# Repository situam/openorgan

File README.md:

# Open Organ

A paraphonic analog synthesizer that offers tangible connections to its circuitry. Touch and moisture sensitive traces let the tunable voices flow into the shaping section. Filter, compressor, vibrato, and mixing modules are built in. Sound is also shaped by its power input, inviting musical interaction with the power source.

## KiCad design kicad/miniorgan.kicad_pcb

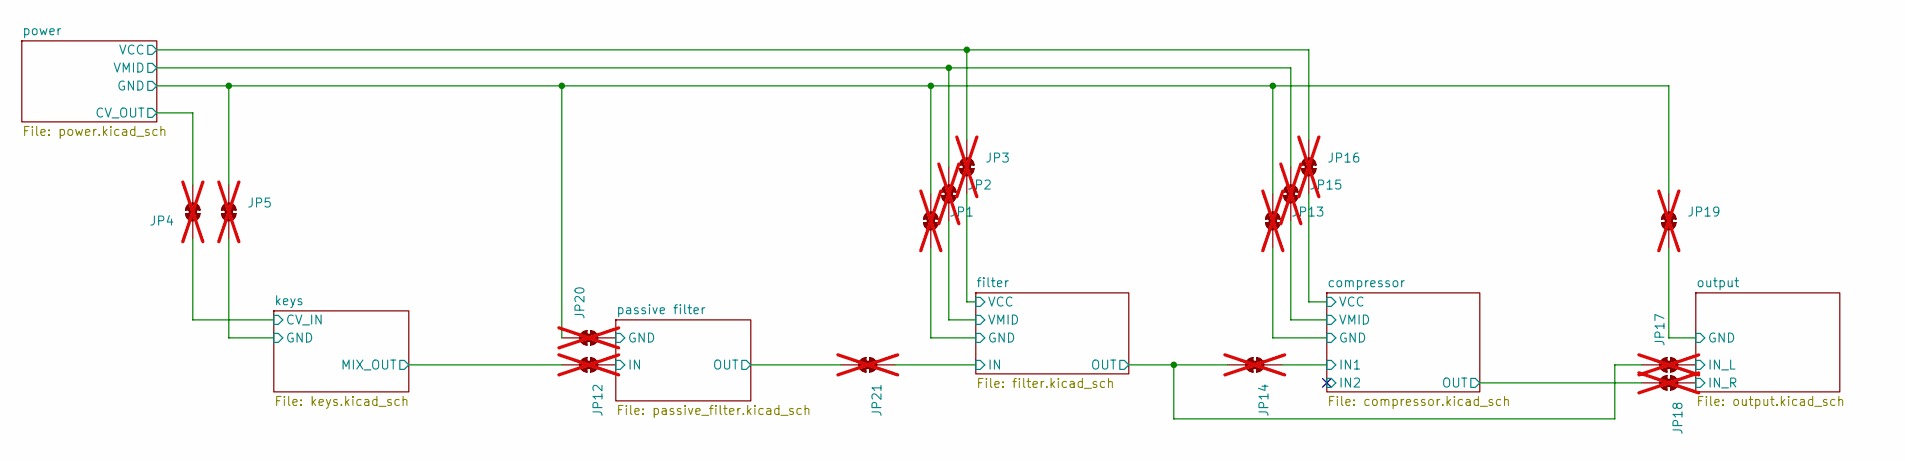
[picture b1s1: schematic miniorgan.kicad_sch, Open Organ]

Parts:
JP1, JP2, JP3, JP4, JP5, JP12, JP13, JP14, JP15, JP16, JP17, JP18, JP19, JP20, JP21: SolderJumper-2_P1.3mm_Bridged_RoundedPad1.0x1.5mm; not fitted

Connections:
/Filter/GND: JP1.2 (B); also elsewhere on the board
/Filter/IN: JP21.1 (A); also elsewhere on the board
/Filter/OUT: JP14.2 (B), JP17.1 (A); also elsewhere on the board
/Filter/VCC: JP3.2 (B); also elsewhere on the board
/Filter/VMID: JP2.2 (B); also elsewhere on the board
/keys/CV_IN: JP4.1 (A); also elsewhere on the board
/keys/GND: JP5.2 (B); also elsewhere on the board
/keys/MIX_OUT: JP12.2 (B); also elsewhere on the board
/output/GND: JP19.2 (B); also elsewhere on the board
/output/IN_L: JP17.2 (B); also elsewhere on the board
/output/IN_R: JP18.1 (A); also elsewhere on the board
/passive filter/GND: JP20.2 (B); also elsewhere on the board
/passive filter/IN: JP12.1 (A); also elsewhere on the board
/passive filter/OUT: JP21.2 (B); also elsewhere on the board
/power/CV_OUT: JP4.2 (B); also elsewhere on the board
/power/GND: JP1.1 (A), JP5.1 (A), JP13.1 (A), JP19.1 (A), JP20.1 (A); also elsewhere on the board
/power/VCC: JP3.1 (A), JP16.1 (A); also elsewhere on the board
/power/VMID: JP2.1 (A), JP15.1 (A); also elsewhere on the board
/vactrol compressor/GND: JP13.2 (B); also elsewhere on the board
/vactrol compressor/IN1: JP14.1 (A); also elsewhere on the board
/vactrol compressor/OUT: JP18.2 (B); also elsewhere on the board
/vactrol compressor/VCC: JP16.2 (B); also elsewhere on the board
/vactrol compressor/VMID: JP15.2 (B); also elsewhere on the board

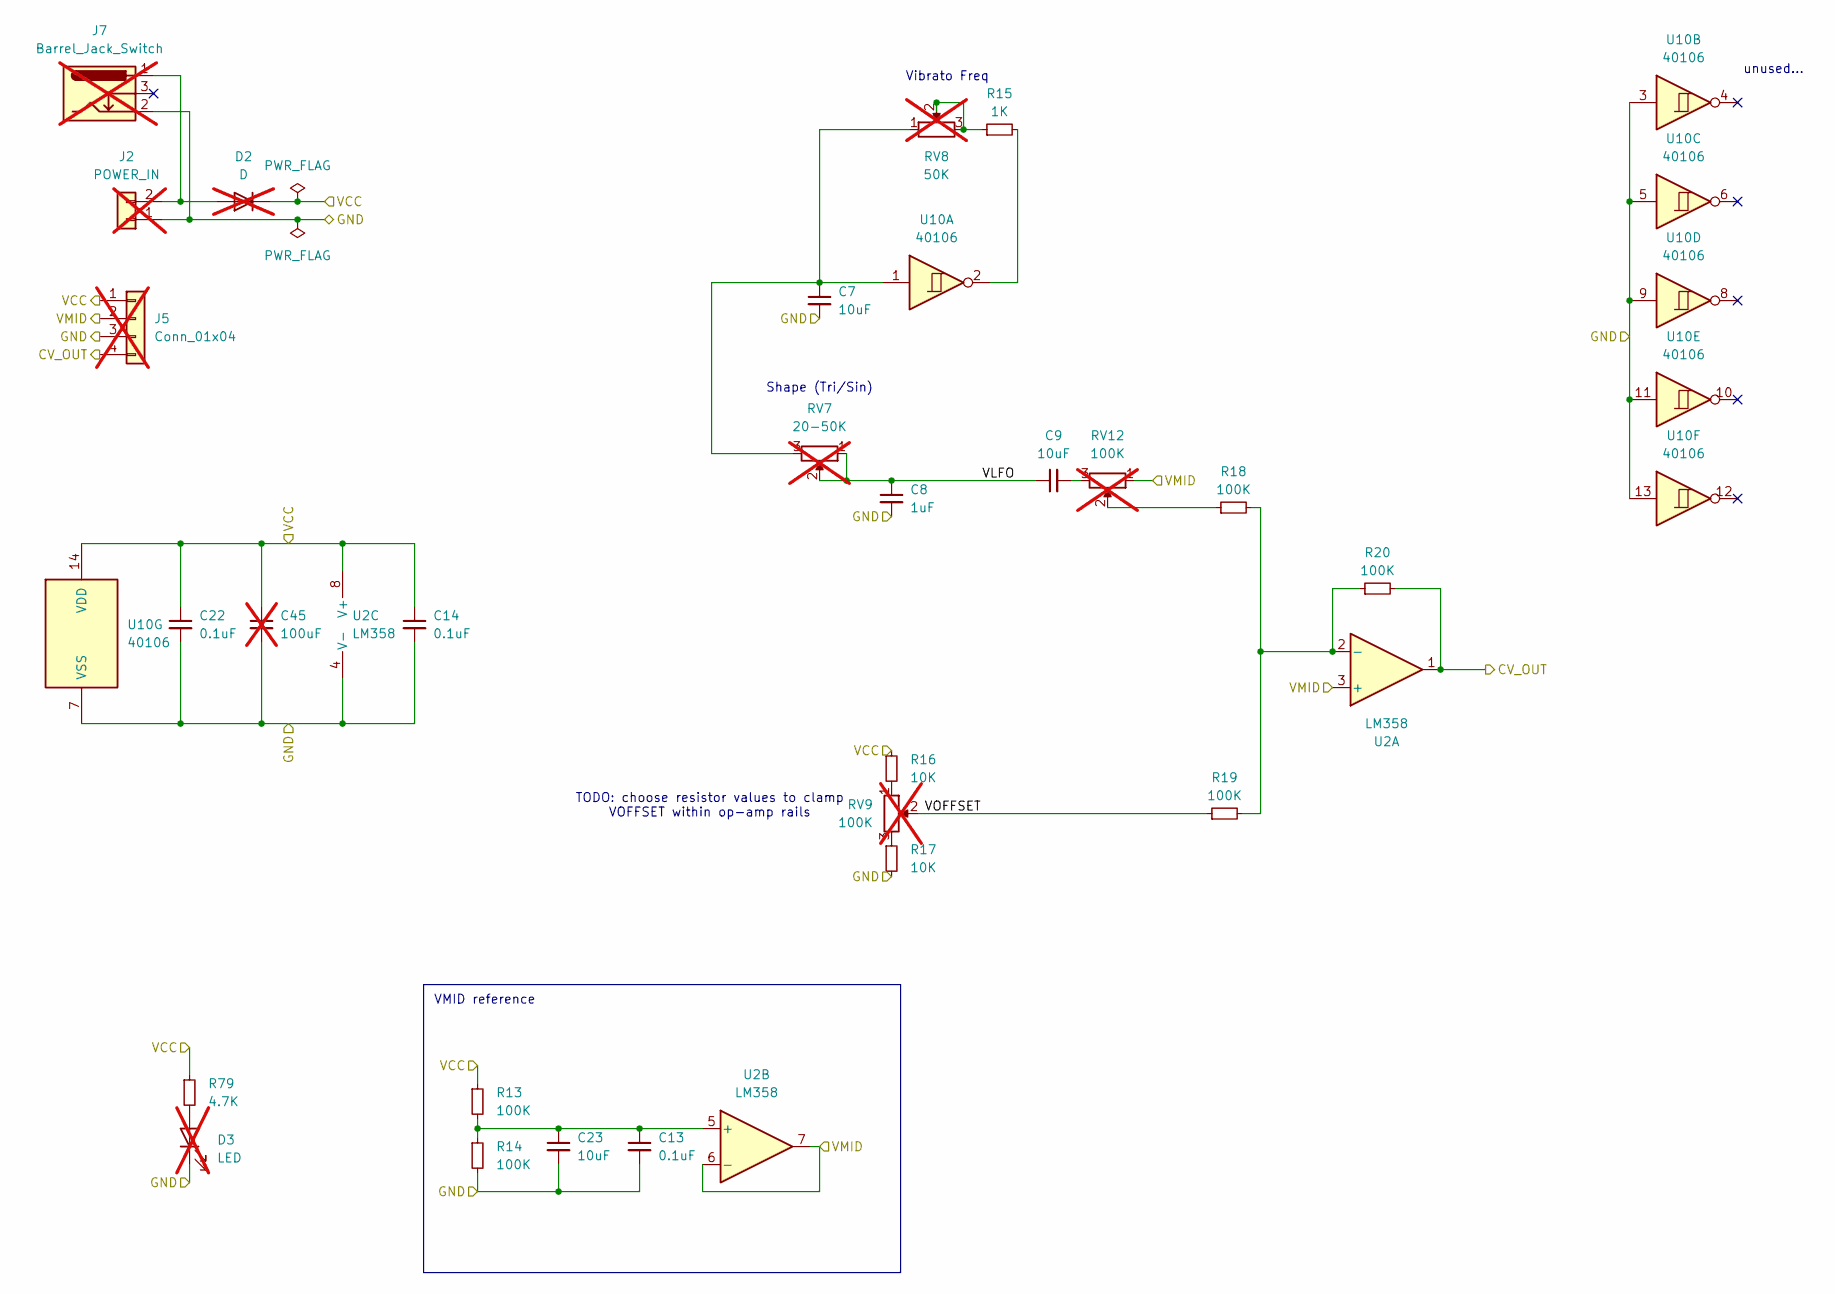
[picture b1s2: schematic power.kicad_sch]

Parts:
C7, C9, C23: 10uF; C_0805_2012Metric
C8: 1uF; C_0805_2012Metric
C13, C14, C22: 0.1uF; C_0805_2012Metric
C45: 100uF; CP_Radial_D7.5mm_P2.50mm; not fitted
D2: D; D_T-1_P2.54mm_Vertical_AnodeUp; not fitted
D3: LED; LED_D3.0mm; not fitted
J2: POWER_IN; PinSocket_1x02_P2.54mm_Vertical; not fitted
J5: Conn_01x04; PinSocket_1x04_P2.54mm_Vertical; not fitted
J7: Barrel_Jack_Switch; BarrelJack_GCT_DCJ200-10-A_Horizontal; not fitted
R13, R14, R18, R19, R20: 100K; R_0603_1608Metric
R15: 1K; R_0603_1608Metric
R16, R17: 10K; R_0603_1608Metric
R79: 4.7K; R_0603_1608Metric
RV7: 20-50K; Pot_RV09AF-ALPHA; not fitted
RV8: 50K; Pot_RV09AF-ALPHA; not fitted
RV9, RV12: 100K; Pot_RV09AF-ALPHA; not fitted
U2: LM358; SOIC-8_L5.0-W4.0-P1.27-LS6.0-BL; JLC C7950
U10: 40106; SOIC-14_L8.7-W3.9-P1.27-LS6.0-BL; JLC C38184

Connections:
/power/CV_OUT: J5.4, R20.2, U2.1; also elsewhere on the board
/power/GND: C7.2, C8.2, C13.2, C14.2, C22.2, C23.2, C45.2, D3.1 (K), J2.1, J5.3, J7.2, R14.2, R17.2, U2.4 (V-), U10.3, U10.5, U10.7 (VSS), U10.9, U10.11, U10.13; also elsewhere on the board
/power/VCC: C14.1, C22.1, C45.1, D2.1 (K), J5.1, R13.1, R16.1, R79.1, U2.8 (V+), U10.14 (VDD); also elsewhere on the board
/power/VLFO: C8.1, C9.1, RV7.1, RV7.2
/power/VMID: J5.2, RV12.1, U2.3 (+), U2.6 (-), U2.7; also elsewhere on the board
/power/VOFFSET: R19.1, RV9.2
unnamed: C7.1, RV7.3, RV8.1, U10.1
unnamed: C9.2, RV12.3
unnamed: D2.2 (A), J2.2, J7.1
unnamed: D3.2 (A), R79.2
unnamed: R15.1, RV8.2, RV8.3
unnamed: R15.2, U10.2
unnamed: R16.2, RV9.1
unnamed: R17.1, RV9.3
unnamed: R18.1, RV12.2
unnamed: R18.2, R19.2, R20.1, U2.2 (-)
unnamed: C13.1, C23.1, R13.2, R14.1, U2.5 (+)

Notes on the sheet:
TODO: choose resistor values to clamp VOFFSET within op-amp rails
Vibrato Freq
Shape (Tri/Sin)
VMID reference
unused...

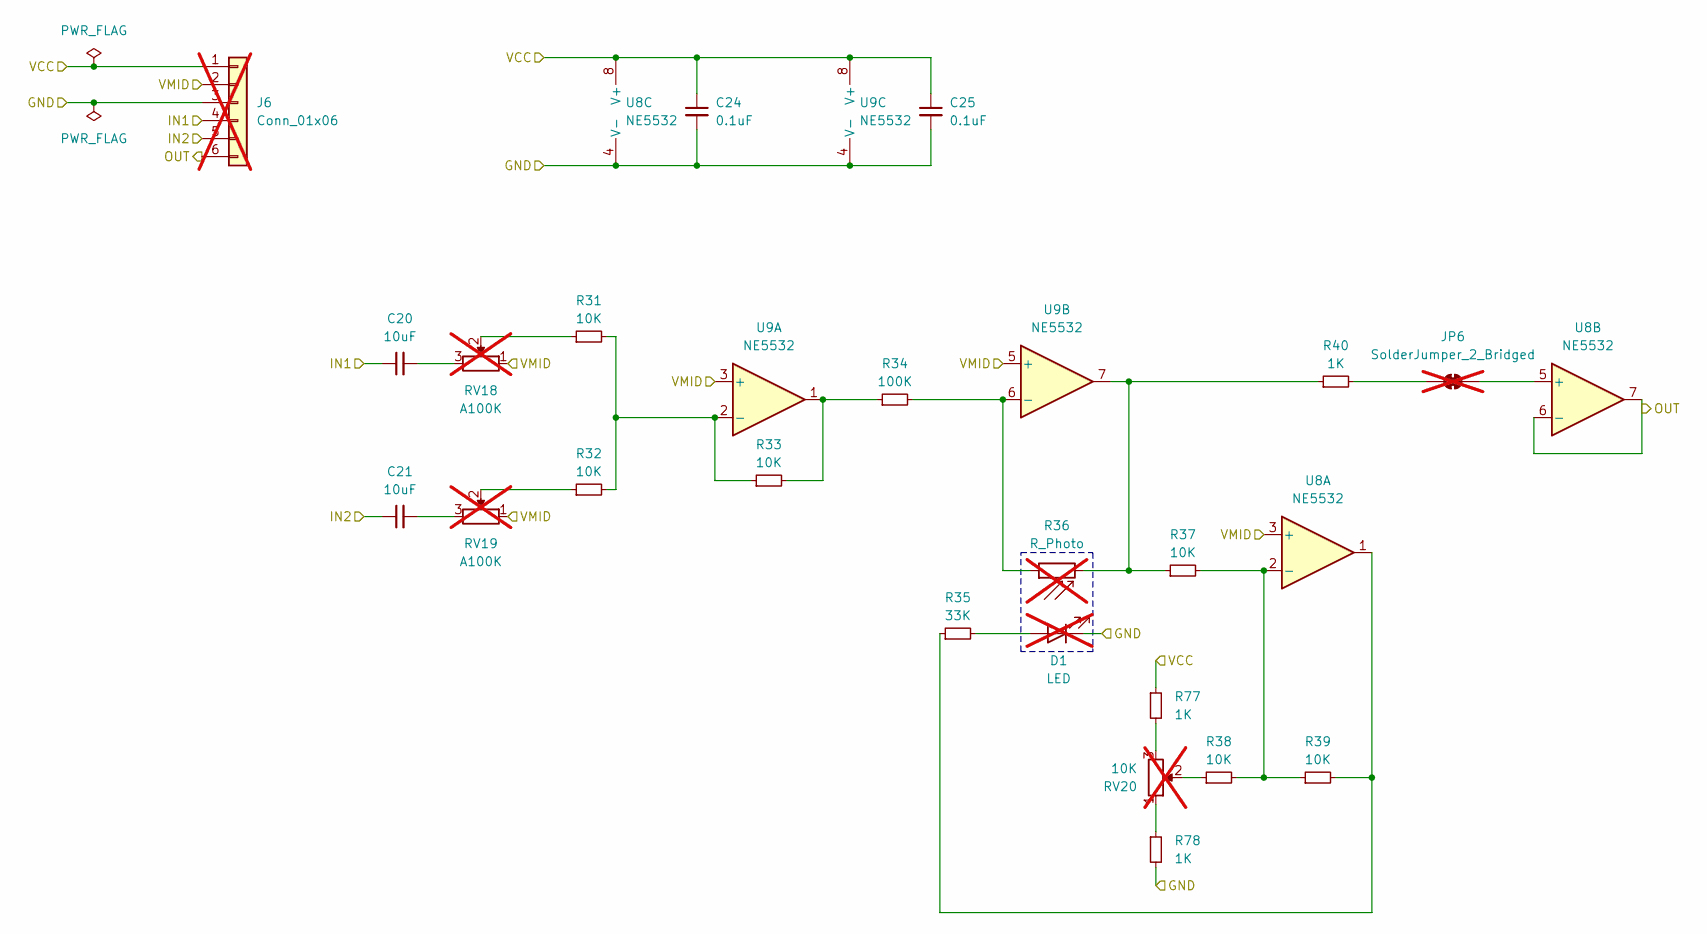
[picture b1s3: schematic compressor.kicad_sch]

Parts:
C20, C21: 10uF; C_0805_2012Metric
C24, C25: 0.1uF; C_0805_2012Metric
D1: LED; LED_D5.0mm_Clear; not fitted
J6: Conn_01x06; PinSocket_1x06_P2.54mm_Vertical; not fitted
JP6: SolderJumper_2_Bridged; SolderJumper-2_P1.3mm_Bridged_RoundedPad1.0x1.5mm; not fitted
R31, R32, R33, R37, R38, R39: 10K; R_0603_1608Metric
R34: 100K; R_0603_1608Metric
R35: 33K; R_0603_1608Metric
R36: R_Photo; R_LDR_4.9x4.2mm_P2.54mm_Vertical; not fitted
R40, R77, R78: 1K; R_0603_1608Metric
RV18, RV19: A100K; Pot_RV09AF-ALPHA; not fitted
RV20: 10K; Pot_RV09AF-ALPHA; not fitted
U8, U9: NE5532; SOIC-8_L4.9-W3.9-P1.27-LS6.0-BL; JLC C7426

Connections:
/vactrol compressor/GND: C24.2, C25.2, D1.1 (K), J6.3, R78.2, U8.4 (V-), U9.4 (V-); also elsewhere on the board
/vactrol compressor/IN1: C20.1, J6.4; also elsewhere on the board
/vactrol compressor/IN2: C21.1, J6.5
/vactrol compressor/OUT: J6.6, U8.6 (-), U8.7; also elsewhere on the board
/vactrol compressor/VCC: C24.1, C25.1, J6.1, R77.1, U8.8 (V+), U9.8 (V+); also elsewhere on the board
/vactrol compressor/VMID: J6.2, RV18.1, RV19.1, U8.3 (+), U9.3 (+), U9.5 (+); also elsewhere on the board
unnamed: C20.2, RV18.3
unnamed: C21.2, RV19.3
unnamed: D1.2 (A), R35.2
unnamed: JP6.1 (A), U8.5 (+)
unnamed: JP6.2 (B), R40.2
unnamed: R31.1, RV18.2
unnamed: R32.1, RV19.2
unnamed: R33.2, R34.1, U9.1
unnamed: R35.1, R39.2, U8.1
unnamed: R36.2, R37.1, R40.1, U9.7
unnamed: R38.1, RV20.2
unnamed: R77.2, RV20.3
unnamed: R78.1, RV20.1
unnamed: R37.2, R38.2, R39.1, U8.2 (-)
unnamed: R31.2, R32.2, R33.1, U9.2 (-)
unnamed: R34.2, R36.1, U9.6 (-)

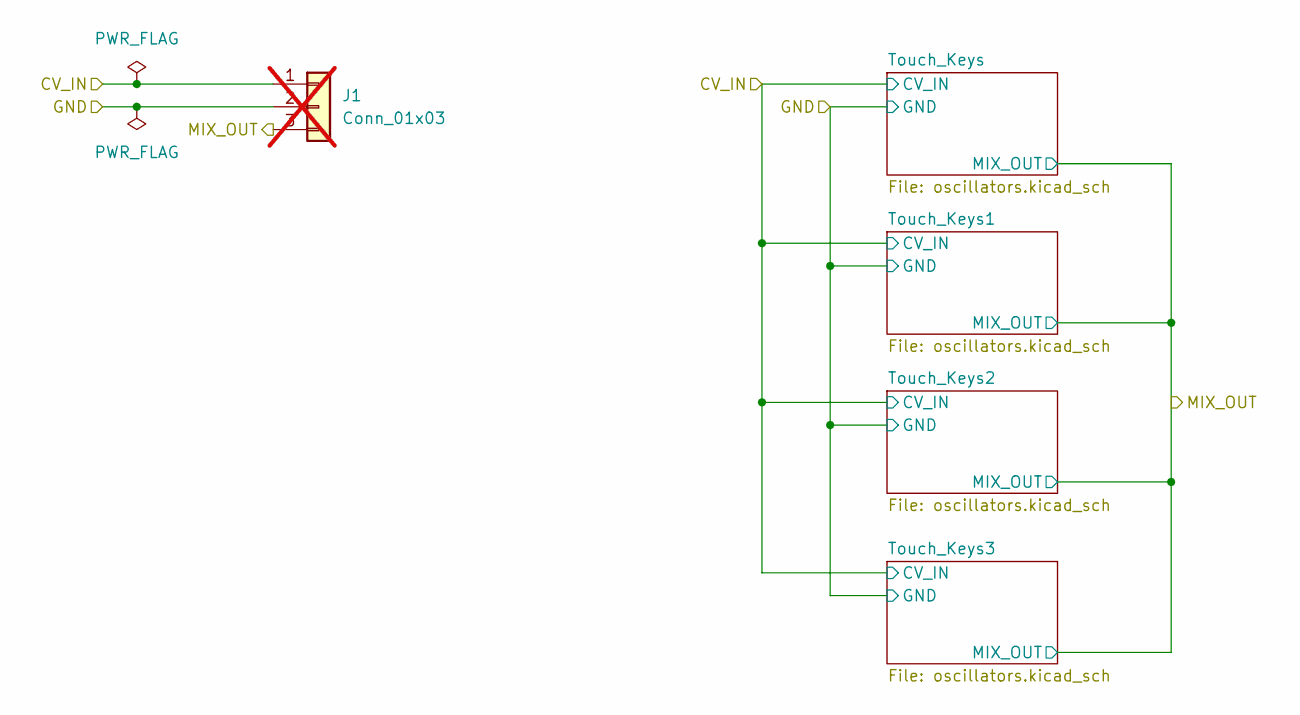
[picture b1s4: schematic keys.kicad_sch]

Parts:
J1: Conn_01x03; PinHeader_1x03_P2.54mm_Vertical; not fitted

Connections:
/keys/CV_IN: J1.1; also elsewhere on the board
/keys/GND: J1.2; also elsewhere on the board
/keys/MIX_OUT: J1.3; also elsewhere on the board

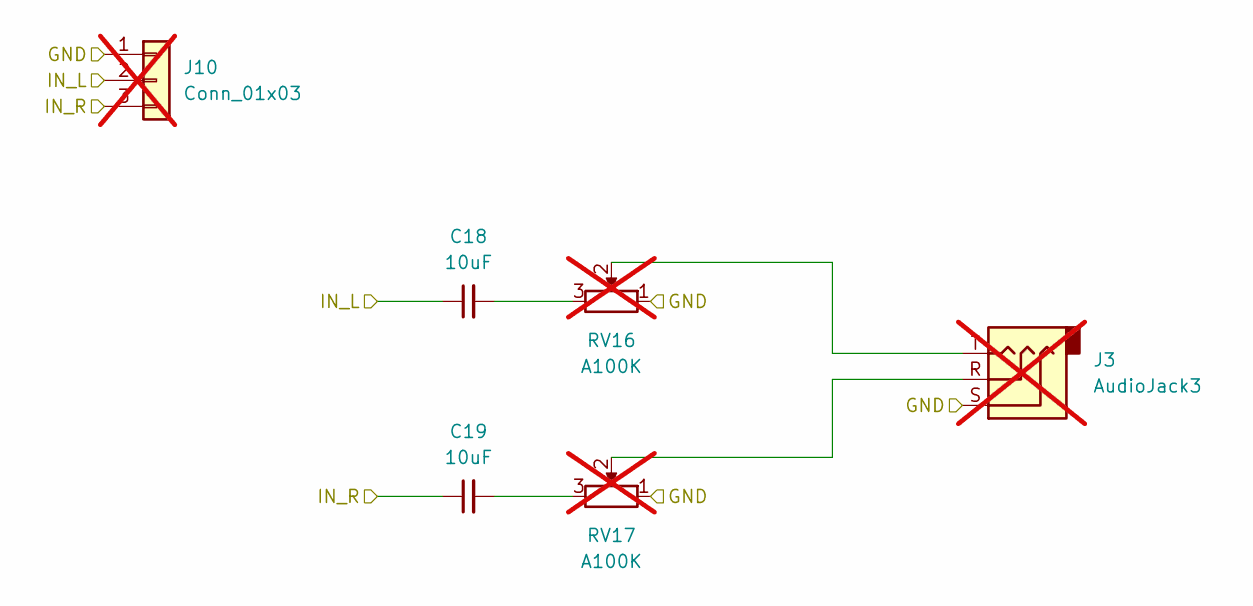
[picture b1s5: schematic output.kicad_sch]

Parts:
C18, C19: 10uF; C_0805_2012Metric
J3: AudioJack3; Jack_3.5mm_CUI_SJ1-3525N_Horizontal; not fitted
J10: Conn_01x03; PinSocket_1x03_P2.54mm_Vertical; not fitted
RV16, RV17: A100K; Pot_RV09AF-ALPHA; not fitted

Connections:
/output/GND: J3.S, J10.1, RV16.1, RV17.1; also elsewhere on the board
/output/IN_L: C18.1, J10.2; also elsewhere on the board
/output/IN_R: C19.1, J10.3; also elsewhere on the board
unnamed: C18.2, RV16.3
unnamed: C19.2, RV17.3
unnamed: J3.R, RV17.2
unnamed: J3.T, RV16.2

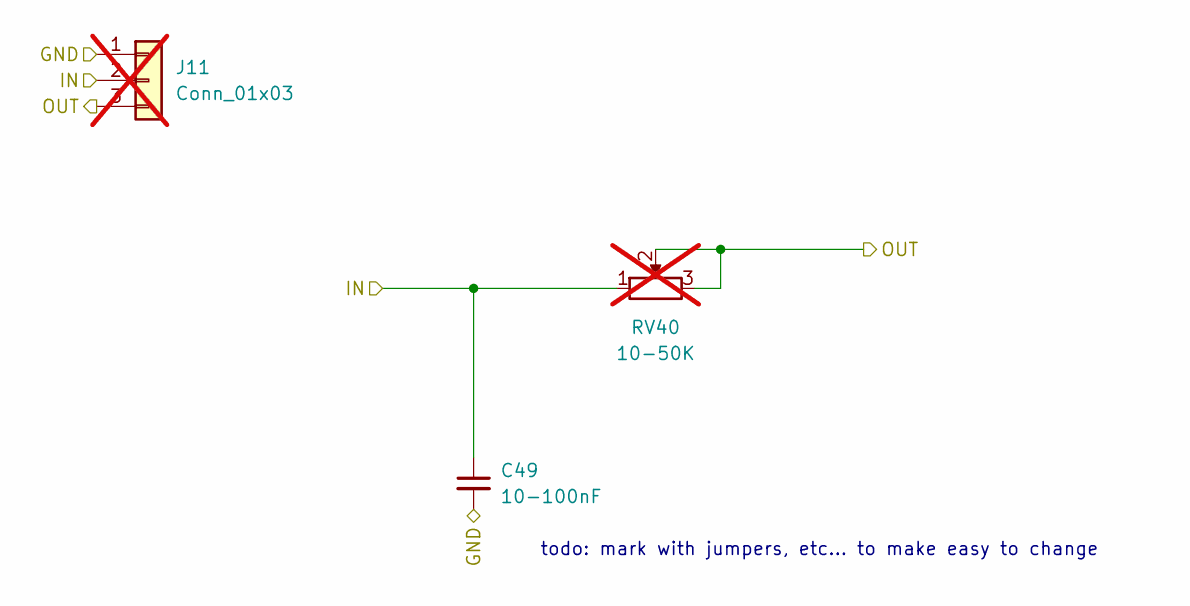
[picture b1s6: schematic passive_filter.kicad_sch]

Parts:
C49: 10-100nF; C_0805_2012Metric
J11: Conn_01x03; PinSocket_1x03_P2.54mm_Vertical; not fitted
RV40: 10-50K; Pot_RV09AF-ALPHA; not fitted

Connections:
/passive filter/GND: C49.2, J11.1; also elsewhere on the board
/passive filter/IN: C49.1, J11.2, RV40.1; also elsewhere on the board
/passive filter/OUT: J11.3, RV40.2, RV40.3; also elsewhere on the board

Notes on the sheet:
todo: mark with jumpers, etc... to make easy to change

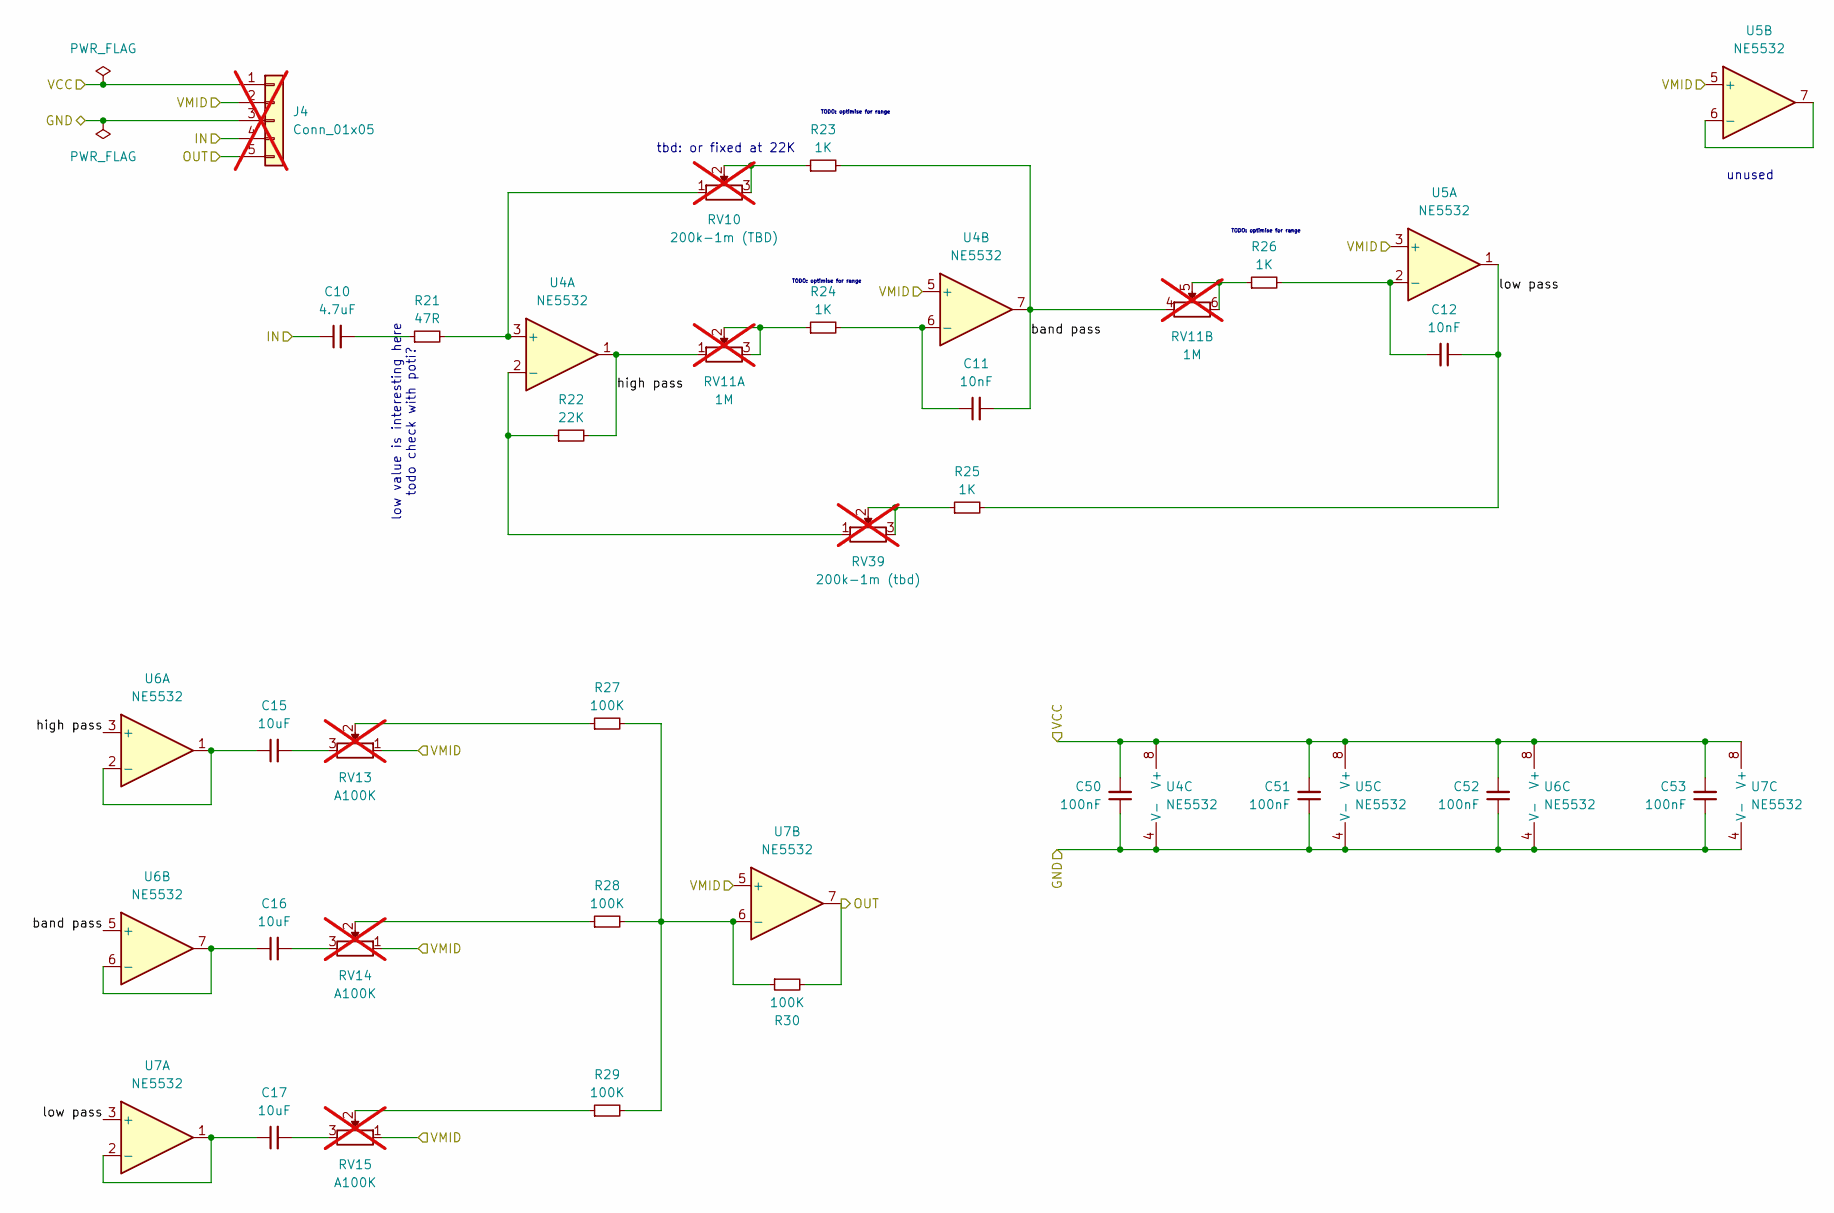
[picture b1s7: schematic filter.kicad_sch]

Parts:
C10: 4.7uF; C_0805_2012Metric
C11, C12: 10nF; C_0805_2012Metric
C15, C16, C17: 10uF; C_0805_2012Metric
C50, C51, C52, C53: 100nF; C_0805_2012Metric
J4: Conn_01x05; PinSocket_1x05_P2.54mm_Vertical; not fitted
R21: 47R; R_0603_1608Metric
R22: 22K; R_0603_1608Metric
R23, R24, R25, R26: 1K; R_0603_1608Metric
R27, R28, R29, R30: 100K; R_0603_1608Metric
RV10: 200k-1m (TBD); Pot_RV09AF-ALPHA; not fitted
RV11: 1M; Potentiometer_Alpha_RD902F-40-00D_Dual_Vertical; not fitted
RV13, RV14, RV15: A100K; Pot_RV09AF-ALPHA; not fitted
RV39: 200k-1m (tbd); Pot_RV09AF-ALPHA; not fitted
U4, U5, U6, U7: NE5532; SOIC-8_L4.9-W3.9-P1.27-LS6.0-BL; JLC C7426

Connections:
/Filter/GND: C50.1, C51.1, C52.1, C53.1, J4.3, U4.4 (V-), U5.4 (V-), U6.4 (V-), U7.4 (V-); also elsewhere on the board
/Filter/IN: C10.1, J4.4; also elsewhere on the board
/Filter/OUT: J4.5, R30.2, U7.7; also elsewhere on the board
/Filter/VCC: C50.2, C51.2, C52.2, C53.2, J4.1, U4.8 (V+), U5.8 (V+), U6.8 (V+), U7.8 (V+); also elsewhere on the board
/Filter/VMID: J4.2, RV13.1, RV14.1, RV15.1, U4.5 (+), U5.3 (+), U5.5 (+), U7.5 (+); also elsewhere on the board
/Filter/band pass: C11.2, R23.2, RV11.4, U4.7, U6.5 (+)
/Filter/high pass: R22.2, RV11.1, U4.1, U6.3 (+)
/Filter/low pass: C12.1, R25.2, U5.1, U7.3 (+)
unnamed: C10.2, R21.1
unnamed: C15.2, RV13.3
unnamed: C16.2, RV14.3
unnamed: C17.2, RV15.3
unnamed: R23.1, RV10.2, RV10.3
unnamed: R24.1, RV11.2, RV11.3
unnamed: R25.1, RV39.2, RV39.3
unnamed: R26.1, RV11.5, RV11.6
unnamed: R27.1, RV13.2
unnamed: R28.1, RV14.2
unnamed: R29.1, RV15.2
unnamed: R21.2, RV10.1, U4.3 (+)
unnamed: R22.1, RV39.1, U4.2 (-)
unnamed: C11.1, R24.2, U4.6 (-)
unnamed: C12.2, R26.2, U5.2 (-)
unnamed: U5.6 (-), U5.7
unnamed: C15.1, U6.1, U6.2 (-)
unnamed: C16.1, U6.6 (-), U6.7
unnamed: C17.1, U7.1, U7.2 (-)
unnamed: R27.2, R28.2, R29.2, R30.1, U7.6 (-)

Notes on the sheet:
TODO: optimise for range
unused
low value is interesting here todo check with poti?
tbd: or fixed at 22K

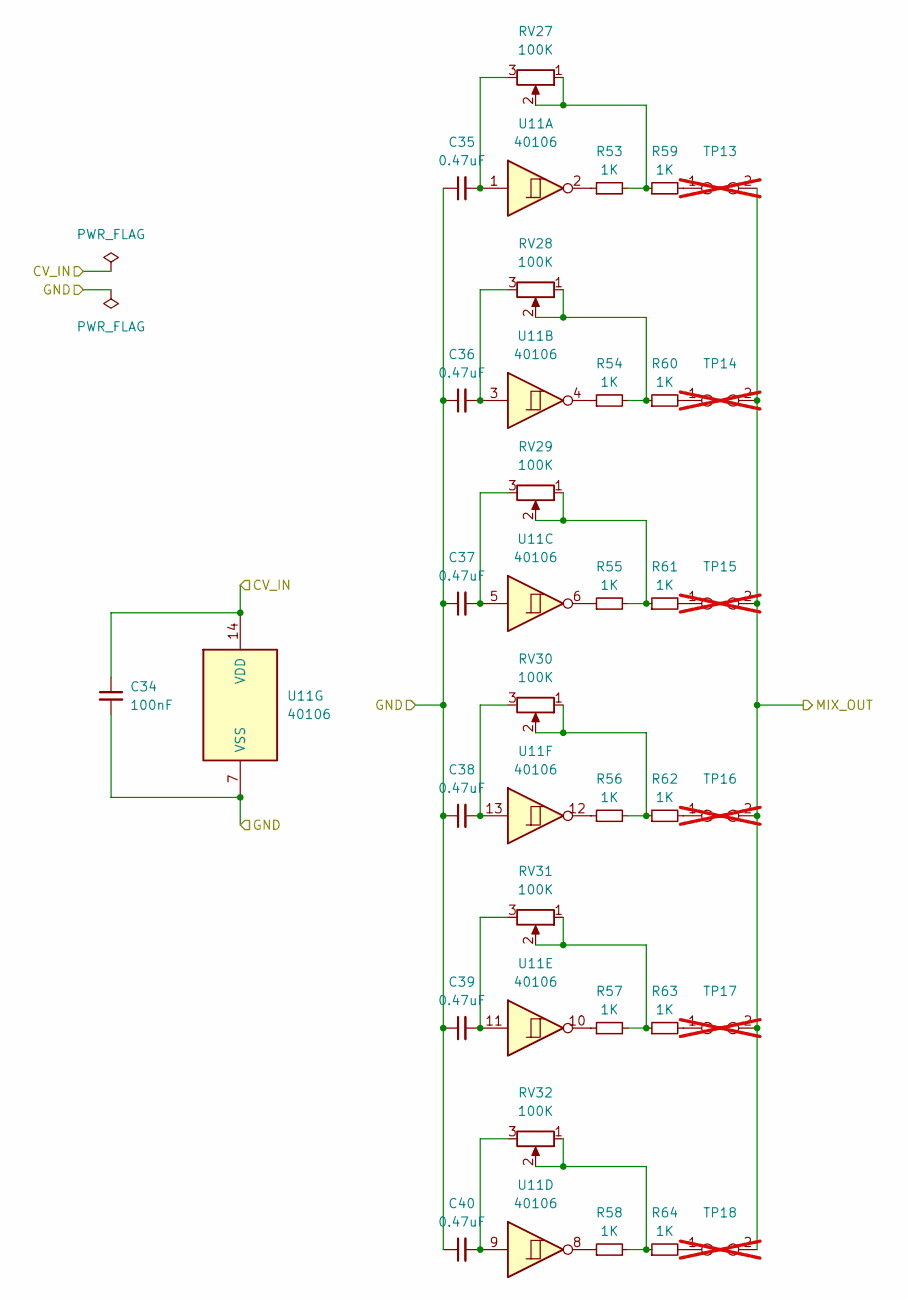
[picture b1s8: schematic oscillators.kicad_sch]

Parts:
C34: 100nF; C_0805_2012Metric
C35, C36, C37, C38, C39, C40: 0.47uF; C_0805_2012Metric
R53, R54, R55, R56, R57, R58, R59, R60, R61, R62, R63, R64: 1K; R_0603_1608Metric
RV27, RV28, RV29, RV30, RV31, RV32: 100K; Potentiometer_Bourns_3296W_Vertical; JLC C118963
TP13, TP14, TP15, TP16, TP17, TP18: key1; TouchPad_2Pole_Square_15x15mm; not fitted
U11: 40106; SOIC-14_L8.7-W3.9-P1.27-LS6.0-BL; JLC C38184

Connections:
/keys/CV_IN: C34.1, U11.14 (VDD); also elsewhere on the board
/keys/GND: C34.2, C35.1, C36.1, C37.1, C38.1, C39.1, C40.1, U11.7 (VSS); also elsewhere on the board
/keys/MIX_OUT: TP13.2, TP14.2, TP15.2, TP16.2, TP17.2, TP18.2; also elsewhere on the board
unnamed: C35.2, RV27.3, U11.1
unnamed: C36.2, RV28.3, U11.3
unnamed: C37.2, RV29.3, U11.5
unnamed: C38.2, RV30.3, U11.13
unnamed: C39.2, RV31.3, U11.11
unnamed: C40.2, RV32.3, U11.9
unnamed: R53.1, U11.2
unnamed: R53.2, R59.1, RV27.1, RV27.2
unnamed: R54.1, U11.4
unnamed: R54.2, R60.1, RV28.1, RV28.2
unnamed: R55.1, U11.6
unnamed: R55.2, R61.1, RV29.1, RV29.2
unnamed: R56.1, U11.12
unnamed: R56.2, R62.1, RV30.1, RV30.2
unnamed: R57.1, U11.10
unnamed: R57.2, R63.1, RV31.1, RV31.2
unnamed: R58.1, U11.8
unnamed: R58.2, R64.1, RV32.1, RV32.2
unnamed: R59.2, TP13.1
unnamed: R60.2, TP14.1
unnamed: R61.2, TP15.1
unnamed: R62.2, TP16.1
unnamed: R63.2, TP17.1
unnamed: R64.2, TP18.1

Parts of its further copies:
C1, C27, C41: 100nF; C_0805_2012Metric
C2, C3, C4, C5, C6, C26, C28, C29, C30, C31, C32, C33, C42, C43, C44, C46, C47, C48: 0.47uF; C_0805_2012Metric
R1, R2, R3, R4, R5, R6, R7, R8, R9, R10, R11, R12, R41, R42, R43, R44, R45, R46, R47, R48, R49, R50, R51, R52, R65, R66, R67, R68, R69, R70, R71, R72, R73, R74, R75, R76: 1K; R_0603_1608Metric
RV1, RV2, RV3, RV4, RV5, RV6, RV21, RV22, RV23, RV24, RV25, RV26, RV33, RV34, RV35, RV36, RV37, RV38: 100K; Potentiometer_Bourns_3296W_Vertical; JLC C118963
TP1, TP2, TP3, TP4, TP5, TP6, TP7, TP8, TP9, TP10, TP11, TP12, TP19, TP20, TP21, TP22, TP23, TP24: key1; TouchPad_2Pole_Square_15x15mm; not fitted
U1, U3, U12: 40106; SOIC-14_L8.7-W3.9-P1.27-LS6.0-BL; JLC C38184

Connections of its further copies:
/keys/CV_IN: C1.1, C27.1, C41.1, U1.14 (VDD), U3.14 (VDD), U12.14 (VDD); also elsewhere on the board
/keys/GND: C1.2, C2.1, C3.1, C4.1, C5.1, C6.1, C26.1, C27.2, C28.1, C29.1, C30.1, C31.1, C32.1, C33.1, C41.2, C42.1, C43.1, C44.1, C46.1, C47.1, C48.1, U1.7 (VSS), U3.7 (VSS), U12.7 (VSS); also elsewhere on the board
/keys/MIX_OUT: TP1.2, TP2.2, TP3.2, TP4.2, TP5.2, TP6.2, TP7.2, TP8.2, TP9.2, TP10.2, TP11.2, TP12.2, TP19.2, TP20.2, TP21.2, TP22.2, TP23.2, TP24.2; also elsewhere on the board
unnamed: C2.2, RV1.3, U1.1
unnamed: C3.2, RV2.3, U1.3
unnamed: C4.2, RV3.3, U1.5
unnamed: C5.2, RV4.3, U1.13
unnamed: C6.2, RV5.3, U1.11
unnamed: C26.2, RV6.3, U1.9
unnamed: C28.2, RV21.3, U3.1
unnamed: C29.2, RV22.3, U3.3
unnamed: C30.2, RV23.3, U3.5
unnamed: C31.2, RV24.3, U3.13
unnamed: C32.2, RV25.3, U3.11
unnamed: C33.2, RV26.3, U3.9
unnamed: C42.2, RV33.3, U12.1
unnamed: C43.2, RV34.3, U12.3
unnamed: C44.2, RV35.3, U12.5
unnamed: C46.2, RV36.3, U12.13
unnamed: C47.2, RV37.3, U12.11
unnamed: C48.2, RV38.3, U12.9
unnamed: R1.1, U1.2
unnamed: R1.2, R7.1, RV1.1, RV1.2
unnamed: R2.1, U1.4
unnamed: R2.2, R8.1, RV2.1, RV2.2
unnamed: R3.1, U1.6
unnamed: R3.2, R9.1, RV3.1, RV3.2
unnamed: R4.1, U1.12
unnamed: R5.1, U1.10
unnamed: R6.1, U1.8
unnamed: R7.2, TP1.1
unnamed: R8.2, TP2.1
unnamed: R9.2, TP3.1
unnamed: R4.2, R10.1, RV4.1, RV4.2
unnamed: R10.2, TP4.1
unnamed: R5.2, R11.1, RV5.1, RV5.2
unnamed: R11.2, TP5.1
unnamed: R6.2, R12.1, RV6.1, RV6.2
unnamed: R12.2, TP6.1
unnamed: R41.1, U3.2
unnamed: R41.2, R47.1, RV21.1, RV21.2
unnamed: R42.1, U3.4
unnamed: R42.2, R48.1, RV22.1, RV22.2
unnamed: R43.1, U3.6
unnamed: R43.2, R49.1, RV23.1, RV23.2
unnamed: R44.1, U3.12
unnamed: R44.2, R50.1, RV24.1, RV24.2
unnamed: R45.1, U3.10
unnamed: R45.2, R51.1, RV25.1, RV25.2
unnamed: R46.1, U3.8
unnamed: R46.2, R52.1, RV26.1, RV26.2
unnamed: R47.2, TP7.1
unnamed: R48.2, TP8.1
unnamed: R49.2, TP9.1
unnamed: R50.2, TP10.1
unnamed: R51.2, TP11.1
unnamed: R52.2, TP12.1
unnamed: R65.1, U12.2
unnamed: R65.2, R71.1, RV33.1, RV33.2
unnamed: R66.1, U12.4
unnamed: R66.2, R72.1, RV34.1, RV34.2
unnamed: R67.1, U12.6
unnamed: R67.2, R73.1, RV35.1, RV35.2
unnamed: R68.1, U12.12
unnamed: R68.2, R74.1, RV36.1, RV36.2
unnamed: R69.1, U12.10
unnamed: R69.2, R75.1, RV37.1, RV37.2
unnamed: R70.1, U12.8
unnamed: R70.2, R76.1, RV38.1, RV38.2
unnamed: R71.2, TP19.1
unnamed: R72.2, TP20.1
unnamed: R73.2, TP21.1
unnamed: R74.2, TP22.1
unnamed: R75.2, TP23.1
unnamed: R76.2, TP24.1

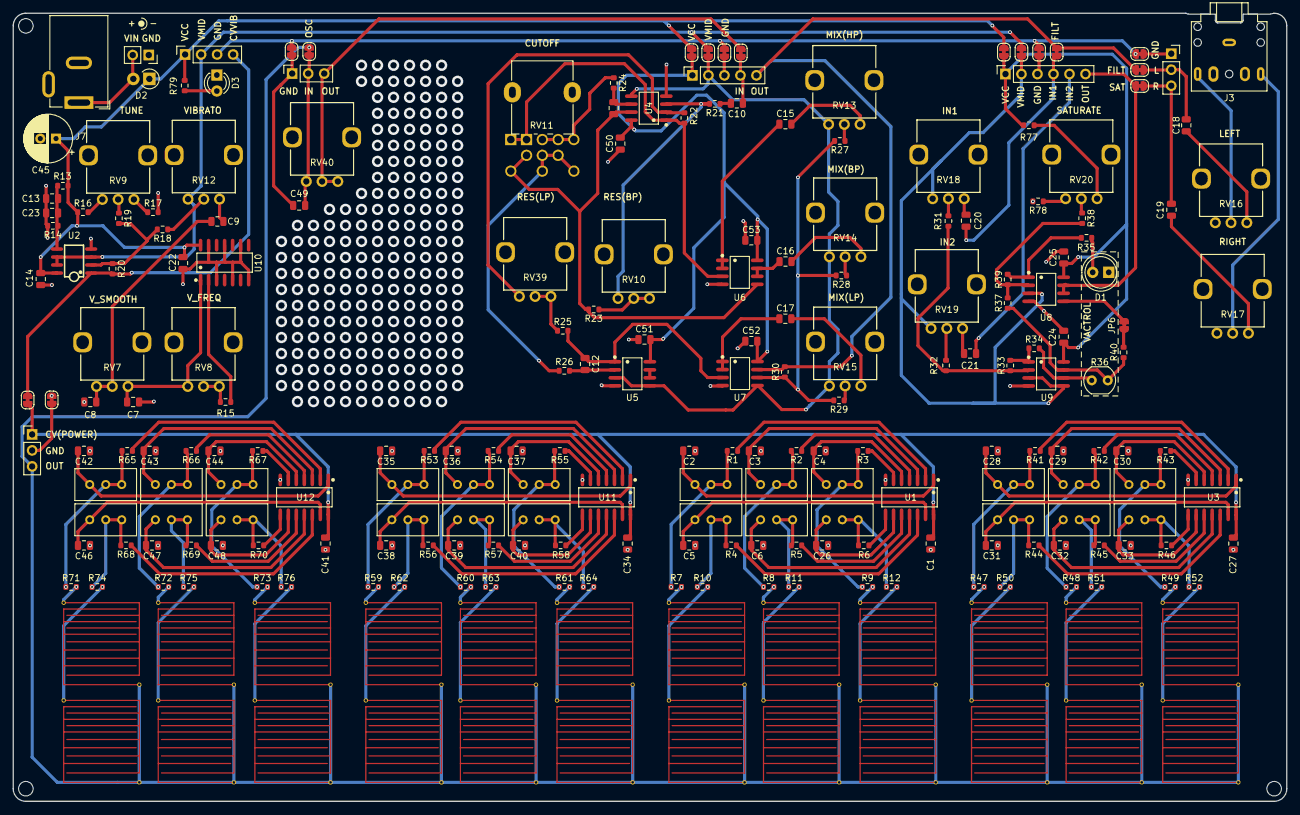
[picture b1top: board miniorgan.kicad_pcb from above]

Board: 2 copper layers, 202.0 x 125.0 mm, 236 parts (0 on the bottom side), 176 nets.

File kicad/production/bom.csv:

Designator,Footprint,Quantity,Value,LCSC Part #
"C1, C27, C34, C41, C50, C51, C52, C53",0805,8,100nF,
C10,0805,1,4.7uF,
"C11, C12",0805,2,10nF,
"C13, C14, C22, C24, C25",0805,5,0.1uF,
"C15, C16, C17, C18, C19, C20, C21, C23, C7, C9",0805,10,10uF,
"C2, C26, C28, C29, C3, C30, C31, C32, C33, C35, C36, C37, C38, C39, C4, C40, C42, C43, C44, C46, C47, C48, C5, C6",0805,24,0.47uF,
C49,0805,1,10-100nF,
C8,0805,1,1uF,
"R1, R10, R11, R12, R15, R2, R23, R24, R25, R26, R3, R4, R40, R41, R42, R43, R44, R45, R46, R47, R48, R49, R5, R50, R51, R52, R53, R54, R55, R56, R57, R58, R59, R6, R60, R61, R62, R63, R64, R65, R66, R67, R68, R69, R7, R70, R71, R72, R73, R74, R75, R76, R77, R78, R8, R9",0603,56,1K,
"R13, R14, R18, R19, R20, R27, R28, R29, R30, R34",0603,10,100K,
"R16, R17, R31, R32, R33, R37, R38, R39",0603,8,10K,
R21,0603,1,47R,
R22,0603,1,22K,
R35,0603,1,33K,
R79,0603,1,4.7K,
"RV1, RV2, RV21, RV22, RV23, RV24, RV25, RV26, RV27, RV28, RV29, RV3, RV30, RV31, RV32, RV33, RV34, RV35, RV36, RV37, RV38, RV4, RV5, RV6",Potentiometer_Bourns_3296W_Vertical,24,100K, C118963
"U1, U10, U11, U12, U3",SOIC-14_L8.7-W3.9-P1.27-LS6.0-BL,5,40106,C38184
U2,SOIC-8_L5.0-W4.0-P1.27-LS6.0-BL,1,LM358,C7950
"U4, U5, U6, U7, U8, U9",SOIC-8_L4.9-W3.9-P1.27-LS6.0-BL,6,NE5532,C7426

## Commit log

2025-02-03 miniorgan v0
2025-02-03 update footprint of dual gang potentiometer to accomodate larger poti
2025-02-03 fix mixers in filter and compressor, update pcb
2025-02-03 mark components as DNP, add LCSC part numbers
2025-11-10 add gitignore
2025-11-10 cleanup
2025-11-10 add license (CC BY-NC-SA 4.0)
2025-11-10 add docs
2025-11-10 add readme
2025-11-10 add local changes
